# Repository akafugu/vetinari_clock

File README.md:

VETINARI CLOCK
==============

Introduction
---

A clock that ticks randomly, but still keeps accurate time!

The idea comes from the Discworld series of books by Sir Terry Pratchett.
Lord Havelock Vetinari is a recurring character in the book series, and he
is in possesion of a very strange clock.

From wikipedia:

"Lord Vetinari also has a strange clock in his waiting-room. While it does keep completely accurate time overall, it sometimes ticks and tocks out of sync (example: "tick, tock... ticktocktick, tock...") and occasionally misses a tick or tock altogether, which has the net effect of turning one's brain "into a sort of porridge". (Feet of Clay, Going Postal). In Feet of Clay Vimes observes that it must have cost him quite a lot of money."

Design files
---

Cad files for Eagle (version 6 or newer) are available in this repository.

Full kits with all required components are also available directly from
[Akafugu Corporation](http://akafugu.jp/posts/products/vetinariclock)

Source code
---

The firmware is a straight port of Simon Inns' original version for PIC12F683
to Attiny25.

The microcontroller is run from a 32kHz crystal, with Timer 1 set up to give
4 overflows each second.

From the original explanation on the webpage:

The firmware has a 'random' sequence of pulses which over 32 seconds moves the
second hand 32 times. This sequence is long enough to give the appearance of
randomness without unnecessarily consuming processor cycles. I chose 32 seconds
as it means the pattern is constantly offset from the 60 second rotation of the
minutes. The 'random' pattern is 128 steps (and is therefore checked 4 times a
second). This means the clock moves between 0-4 times within each actual second.
By moving more or less in each of the 32 seconds the clock looks random, however
the sequence always moves the clock exactly 32 seconds in the 128 steps.

Attribution
---

Original project and code for PIC PIC12F683 by Simon Inns:

http://www.waitingforfriday.com/index.php/Vetinari%27s_Clock

avr-gcc port for Attiny25 by Akafugu Corporation:

http://akafugu.jp/posts/products/vetinariclock

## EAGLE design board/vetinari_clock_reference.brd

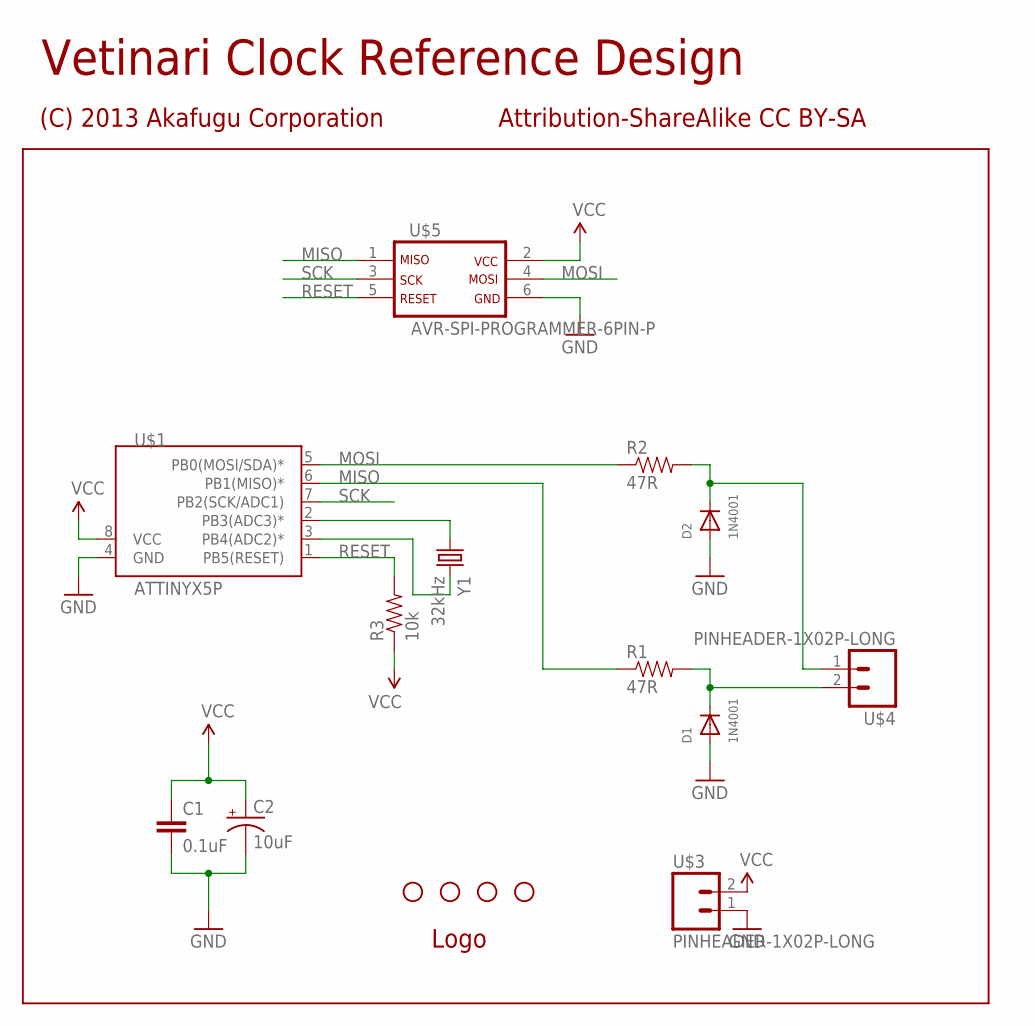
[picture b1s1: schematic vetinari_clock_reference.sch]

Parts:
C1: 0.1uF; CAP-PTH-2.54MM
C2: 10uF; CPOL-RADIAL-SLIM
D1, D2: 1N4001; DIODE-1N4001-BIGHOLES
JP1, JP2, JP3, JP4: STAND-OFF
R1, R2: 47R; 1/6W-RES-OUTLINE
R3: 10k; 1/6W-RES-OUTLINE
U$1: ATTINYX5P; DIL-8
U$3, U$4: PINHEADER-1X02P-LONG; 1X02-LONG
U$5: AVR-SPI-PROGRAMMER-6PIN-P; 2X03
U$6: OSHW-LOGO-OUTLINE
Y1: 32kHz; TC38H

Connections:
GND: C1.2, C2.2 (-), D1.A, D2.A, U$1.4 (GND), U$3.1, U$5.6
MISO: R1.1, U$1.6 (PB1(MISO)*), U$5.1
MOSI: R2.1, U$1.5 (PB0(MOSI/SDA)*), U$5.4
unnamed: D1.C, R1.2, U$4.2
unnamed: U$1.2 (PB3(ADC3)*), Y1.1
unnamed: U$1.3 (PB4(ADC2)*), Y1.2
unnamed: D2.C, R2.2, U$4.1
RESET: R3.2, U$1.1 (PB5(RESET)), U$5.5
SCK: U$1.7 (PB2(SCK/ADC1)), U$5.3
VCC: C1.1, C2.1 (+), R3.1, U$1.8 (VCC), U$3.2, U$5.2

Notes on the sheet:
Vetinari Clock Reference Design
(C) 2013 Akafugu Corporation
Attribution-ShareAlike CC BY-SA

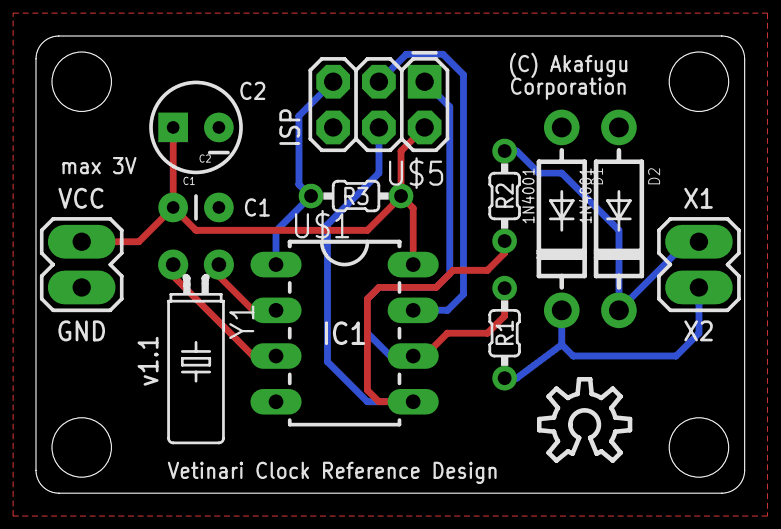
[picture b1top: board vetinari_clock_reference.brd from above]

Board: 2 copper layers, 39.4 x 25.4 mm, 17 parts (0 on the bottom side), 10 nets.

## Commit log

2013-02-27 Original version for PIC12F683
2013-02-27 Ported to ATTiny25
2013-03-27 Added .gitignore
2013-03-30 Add compensation for slowness
2013-03-30 Eagle reference design
2013-03-31 Cleaned up comments
2013-03-31 1pps version
2013-03-31 almost_normal initial version
2013-04-05 Data space overflow fix
2013-04-05 Fix for battery consumption. Cleanup
2013-12-27 Changed ENERGISE_TIME to match new clock mechanism
2014-12-13 Further increase of ENERGISE_TIME
